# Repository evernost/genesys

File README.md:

# genesys
Audio processing on a custom STM32 board.

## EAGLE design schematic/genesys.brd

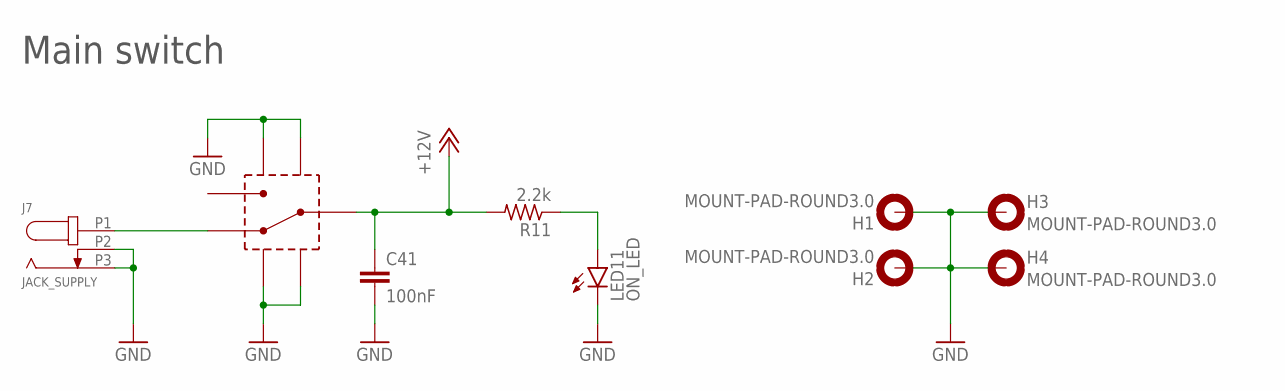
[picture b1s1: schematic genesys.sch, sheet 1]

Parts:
C41: 100nF; C0805K
H1, H2, H3, H4: MOUNT-PAD-ROUND3.0; 3,0-PAD
J7: JACK_SUPPLY; DC-10LP
LED11: ON_LED; CHIPLED_0603
R11: 2.2k; R0603
S1: SWITCH_1P

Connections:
+12V: C41.1, R11.2, S1.P2; also elsewhere on the board
GND: C41.2, H1.B3,0, H2.B3,0, H3.B3,0, H4.B3,0, J7.P2, J7.P3, LED11.C, S1.SHIELD@1 (SHIELD), S1.SHIELD@2 (SHIELD), S1.SHIELD@3 (SHIELD), S1.SHIELD@4 (SHIELD); also elsewhere on the board
unnamed: J7.P1, S1.P1
unnamed: LED11.A, R11.1

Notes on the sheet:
Main switch

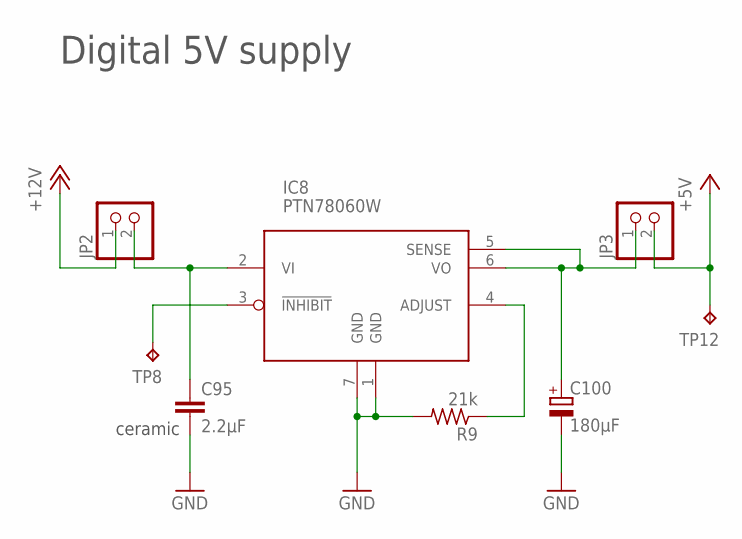
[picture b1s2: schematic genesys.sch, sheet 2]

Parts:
C95: 2.2µF; C1206
C100: 180µF; E3,5-8
IC8: PTN78060W; R-PDSS-T7
JP2, JP3: PINHD-1X2; 1X02
R9: 21k; R0805
TP8, TP12: TPTP15R; TP15R

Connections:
+5V: JP3.2, TP12.TP; also elsewhere on the board
+12V: JP2.1; also elsewhere on the board
GND: C95.2, C100.-, IC8.1 (GND), IC8.7 (GND), R9.2; also elsewhere on the board
unnamed: C95.1, IC8.2 (VI), JP2.2
unnamed: C100.+, IC8.5 (SENSE), IC8.6 (VO), JP3.1
unnamed: IC8.3 (!INHIBIT), TP8.TP
unnamed: IC8.4 (ADJUST), R9.1

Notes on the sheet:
Digital 5V supply
ceramic

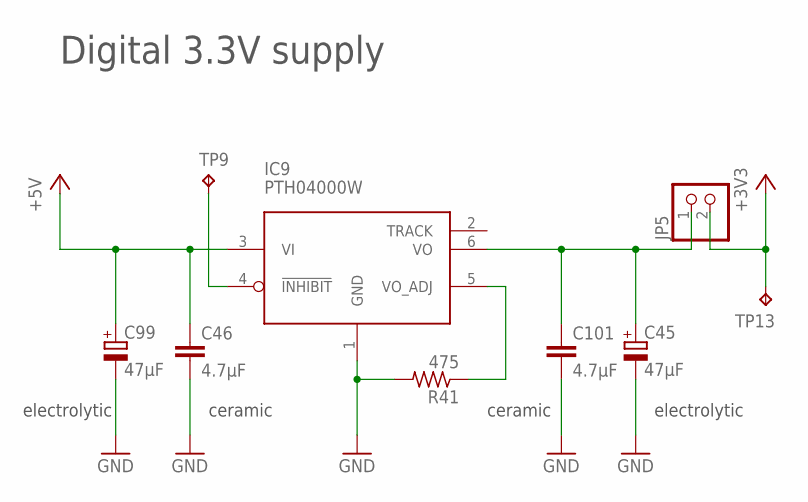
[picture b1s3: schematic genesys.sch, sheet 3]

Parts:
C45, C99: 47µF; E2,5-7
C46, C101: 4.7µF; C0805K
IC9: PTH04000W; R-PDSS-T6
JP5: PINHD-1X2; 1X02
R41: 475; R0805
TP9, TP13: TPTP15R; TP15R

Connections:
+3V3: JP5.2, TP13.TP; also elsewhere on the board
+5V: C46.1, C99.+, IC9.3 (VI); also elsewhere on the board
GND: C45.-, C46.2, C99.-, C101.2, IC9.1 (GND), R41.2; also elsewhere on the board
unnamed: IC9.5 (VO_ADJ), R41.1
unnamed: IC9.4 (!INHIBIT), TP9.TP
unnamed: C45.+, C101.1, IC9.6 (VO), JP5.1
TRACK: IC9.2 (TRACK)

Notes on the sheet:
Digital 3.3V supply
electrolytic
ceramic

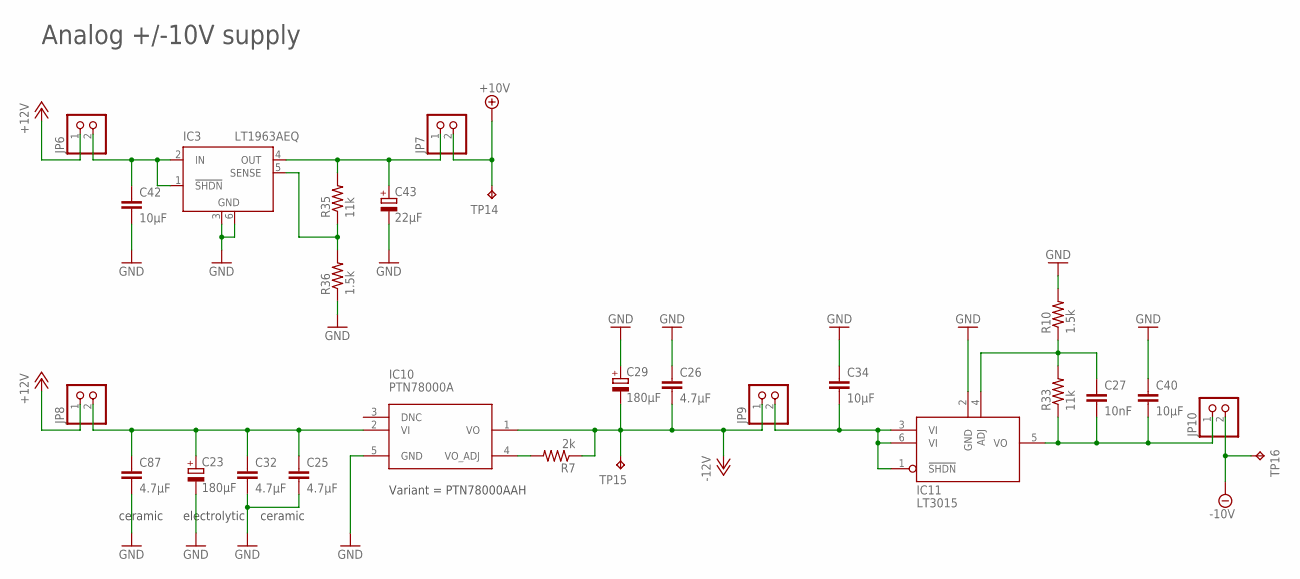
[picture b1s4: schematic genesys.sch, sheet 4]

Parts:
C23, C29: 180µF; E3,5-8
C25, C26, C32, C87: 4.7µF; C0805K
C27: 10nF; C0805K
C34, C40, C42: 10µF; C0805K
C43: 22µF; CT3528
IC3: LT1963AEQ; Q5-DD
IC10: PTN78000A; R-PDSS-T5
IC11: LT3015; Q5-DD
JP6, JP7, JP8, JP9, JP10: PINHD-1X2; 1X02
R7: 2k; R0805
R10, R36: 1.5k; R0805
R33, R35: 11k; R0805
TP14, TP15, TP16: TPTP15R; TP15R

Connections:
+10V: JP7.2, TP14.TP; also elsewhere on the board
+12V: JP6.1, JP8.1; also elsewhere on the board
-10V: JP10.2, TP16.TP; also elsewhere on the board
-12V: C26.2, C29.-, IC10.1 (VO), JP9.1, R7.1, TP15.TP
GND: C23.-, C25.2, C26.1, C29.+, C32.2, C34.1, C40.1, C42.2, C43.-, C87.2, IC3.3 (GND), IC3.6 (GND), IC10.5 (GND), IC11.2 (GND), R10.2, R36.1; also elsewhere on the board
unnamed: IC3.5 (SENSE), R35.1, R36.2
unnamed: IC10.4 (VO_ADJ), R7.2
unnamed: C27.1, IC11.4 (ADJ), R10.1, R33.2
unnamed: C42.1, IC3.1 (!SHDN), IC3.2 (IN), JP6.2
unnamed: C43.+, IC3.4 (OUT), JP7.1, R35.2
unnamed: C34.2, IC11.1 (!SHDN), IC11.3 (VI), IC11.6 (VI), JP9.2
unnamed: C23.+, C25.1, C32.1, C87.1, IC10.2 (VI), JP8.2
unnamed: C27.2, C40.2, IC11.5 (VO), JP10.1, R33.1

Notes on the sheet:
Analog +/-10V supply
ceramic
electrolytic
Variant = PTN78000AAH

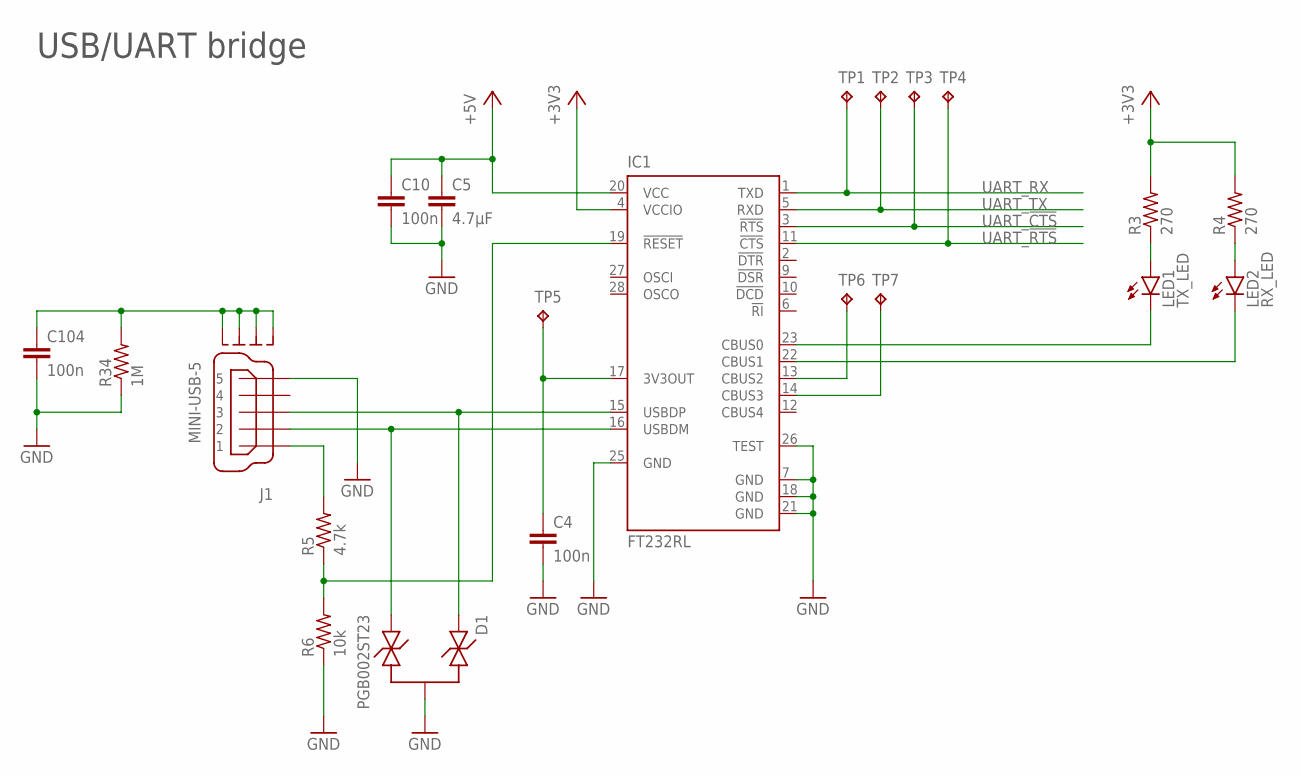
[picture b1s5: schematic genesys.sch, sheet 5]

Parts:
C4, C10, C104: 100n; C0805K
C5: 4.7µF; C0805K
D1: PGB002ST23; SOT23
IC1: FT232RL; SSOP28
J1: MINI-USB-5; 56579-0579
LED1: TX_LED; CHIPLED_0603
LED2: RX_LED; CHIPLED_0603
R3, R4: 270; R0603
R5: 4.7k; R0603
R6: 10k; R0603
R34: 1M; R0603
TP1, TP2, TP3, TP4, TP5, TP6, TP7: TPTP15R; TP15R

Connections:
+3V3: IC1.4 (VCCIO), R3.2, R4.2; also elsewhere on the board
+5V: C5.1, C10.1, IC1.20 (VCC); also elsewhere on the board
GND: C4.2, C5.2, C10.2, C104.2, D1.3, IC1.7 (GND), IC1.18 (GND), IC1.21 (GND), IC1.25 (GND), IC1.26 (TEST), J1.GND (5), R6.1, R34.1; also elsewhere on the board
unnamed: C4.1, IC1.17 (3V3OUT), TP5.TP
unnamed: IC1.23 (CBUS0), LED1.C
unnamed: IC1.22 (CBUS1), LED2.C
unnamed: LED1.A, R3.1
unnamed: LED2.A, R4.1
unnamed: D1.2, IC1.16 (USBDM), J1.DN (2)
unnamed: J1.VBUS (1), R5.2
unnamed: IC1.19 (!RESET), R5.1, R6.2
unnamed: D1.1, IC1.15 (USBDP), J1.DP (3)
unnamed: IC1.13 (CBUS2), TP6.TP
unnamed: IC1.14 (CBUS3), TP7.TP
unnamed: C104.1, J1.SHIELD@1 (S1), J1.SHIELD@2 (S2), J1.SHIELD@3 (S3), J1.SHIELD@4 (S4), R34.2
UART_!CTS: IC1.3 (!RTS), TP3.TP; also elsewhere on the board
UART_!RTS: IC1.11 (!CTS), TP4.TP; also elsewhere on the board
UART_RX: IC1.1 (TXD), TP1.TP; also elsewhere on the board
UART_TX: IC1.5 (RXD), TP2.TP; also elsewhere on the board

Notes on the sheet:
USB/UART bridge

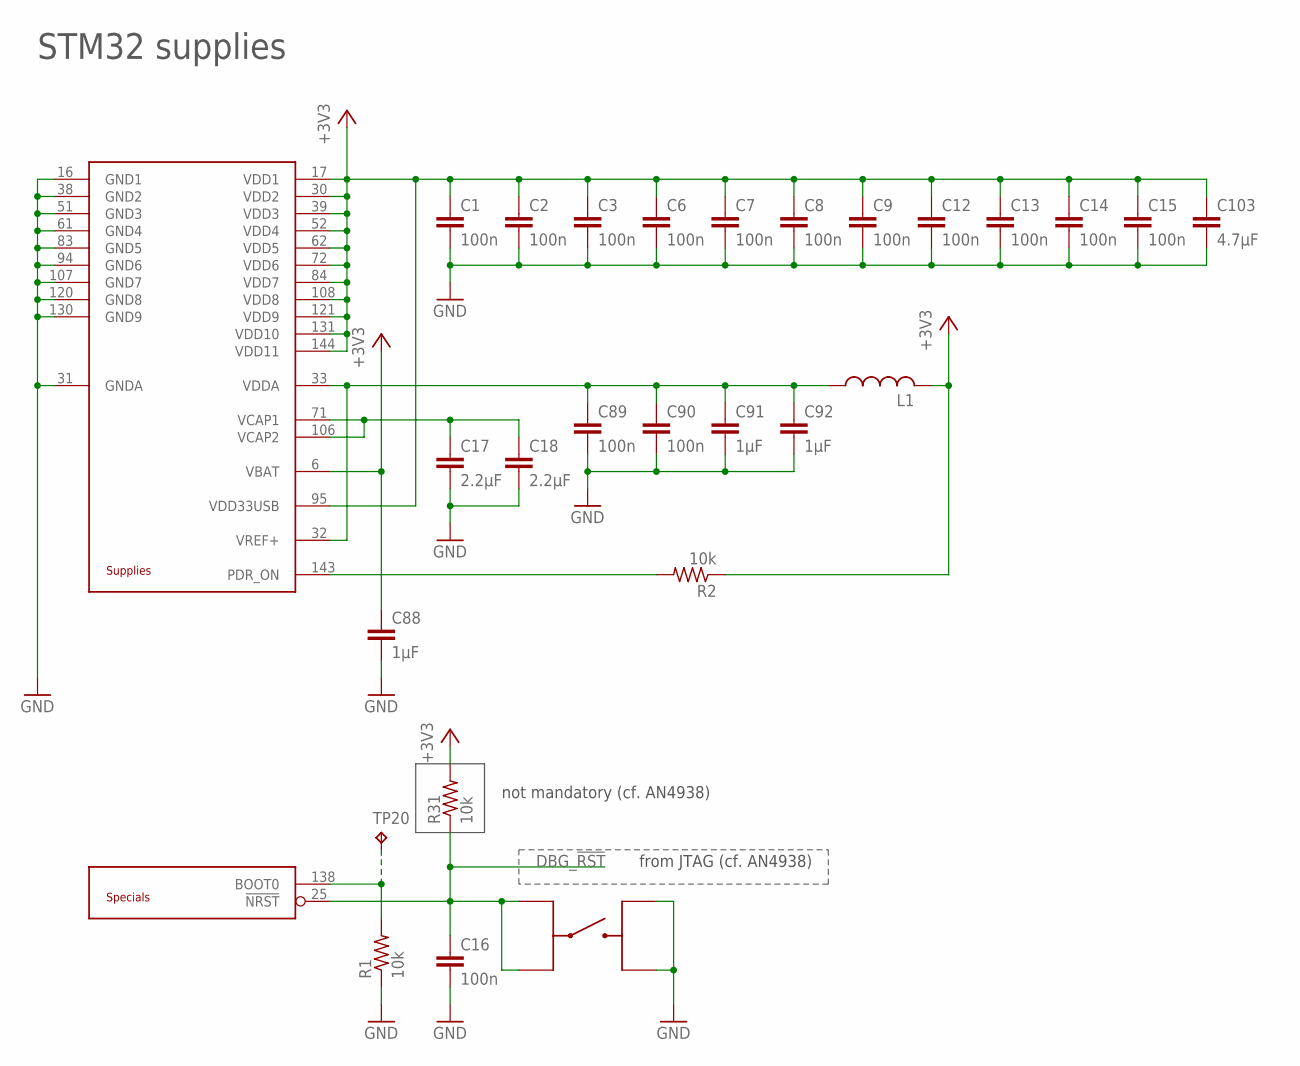
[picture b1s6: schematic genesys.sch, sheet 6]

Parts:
B1: KSC521G
C1, C2, C3, C6, C7, C8, C9, C12, C13, C14, C15, C16, C89, C90: 100n; C0805K
C17, C18: 2.2µF; C0805K
C88, C91, C92: 1µF; C0805K
C103: 4.7µF; C0805K
L1: L-USL3216C; L3216C
R1, R2, R31: 10k; R0805
TP20: TPTP15R; TP15R
U$1: STM32H743ZI; TQFP144

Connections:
+3V3: C1.1, C2.1, C3.1, C6.1, C7.1, C8.1, C9.1, C12.1, C13.1, C14.1, C15.1, C88.1, C103.1, L1.2, R2.1, R31.2, U$1.6 (VBAT), U$1.17 (VDD1), U$1.30 (VDD2), U$1.39 (VDD3), U$1.52 (VDD4), U$1.62 (VDD5), U$1.72 (VDD6), U$1.84 (VDD7), U$1.95 (VDD33USB), U$1.108 (VDD8), U$1.121 (VDD9), U$1.131 (VDD10), U$1.144 (VDD11); also elsewhere on the board
DBG_!RST: B1.3, B1.4, C16.1, R31.1, U$1.25 (!NRST); also elsewhere on the board
GND: B1.1, B1.2, C1.2, C2.2, C3.2, C6.2, C7.2, C8.2, C9.2, C12.2, C13.2, C14.2, C15.2, C16.2, C17.2, C18.2, C88.2, C89.2, C90.2, C91.2, C92.2, C103.2, R1.1, U$1.16 (GND1), U$1.31 (GNDA), U$1.38 (GND2), U$1.51 (GND3), U$1.61 (GND4), U$1.83 (GND5), U$1.94 (GND6), U$1.107 (GND7), U$1.120 (GND8), U$1.130 (GND9); also elsewhere on the board
unnamed: R1.2, TP20.TP, U$1.138 (BOOT0)
unnamed: C89.1, C90.1, C91.1, C92.1, L1.1, U$1.32 (VREF+), U$1.33 (VDDA)
unnamed: R2.2, U$1.143 (PDR_ON)
unnamed: C17.1, C18.1, U$1.71 (VCAP1), U$1.106 (VCAP2)

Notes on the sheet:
STM32 supplies
not mandatory (cf. AN4938)
from JTAG (cf. AN4938)

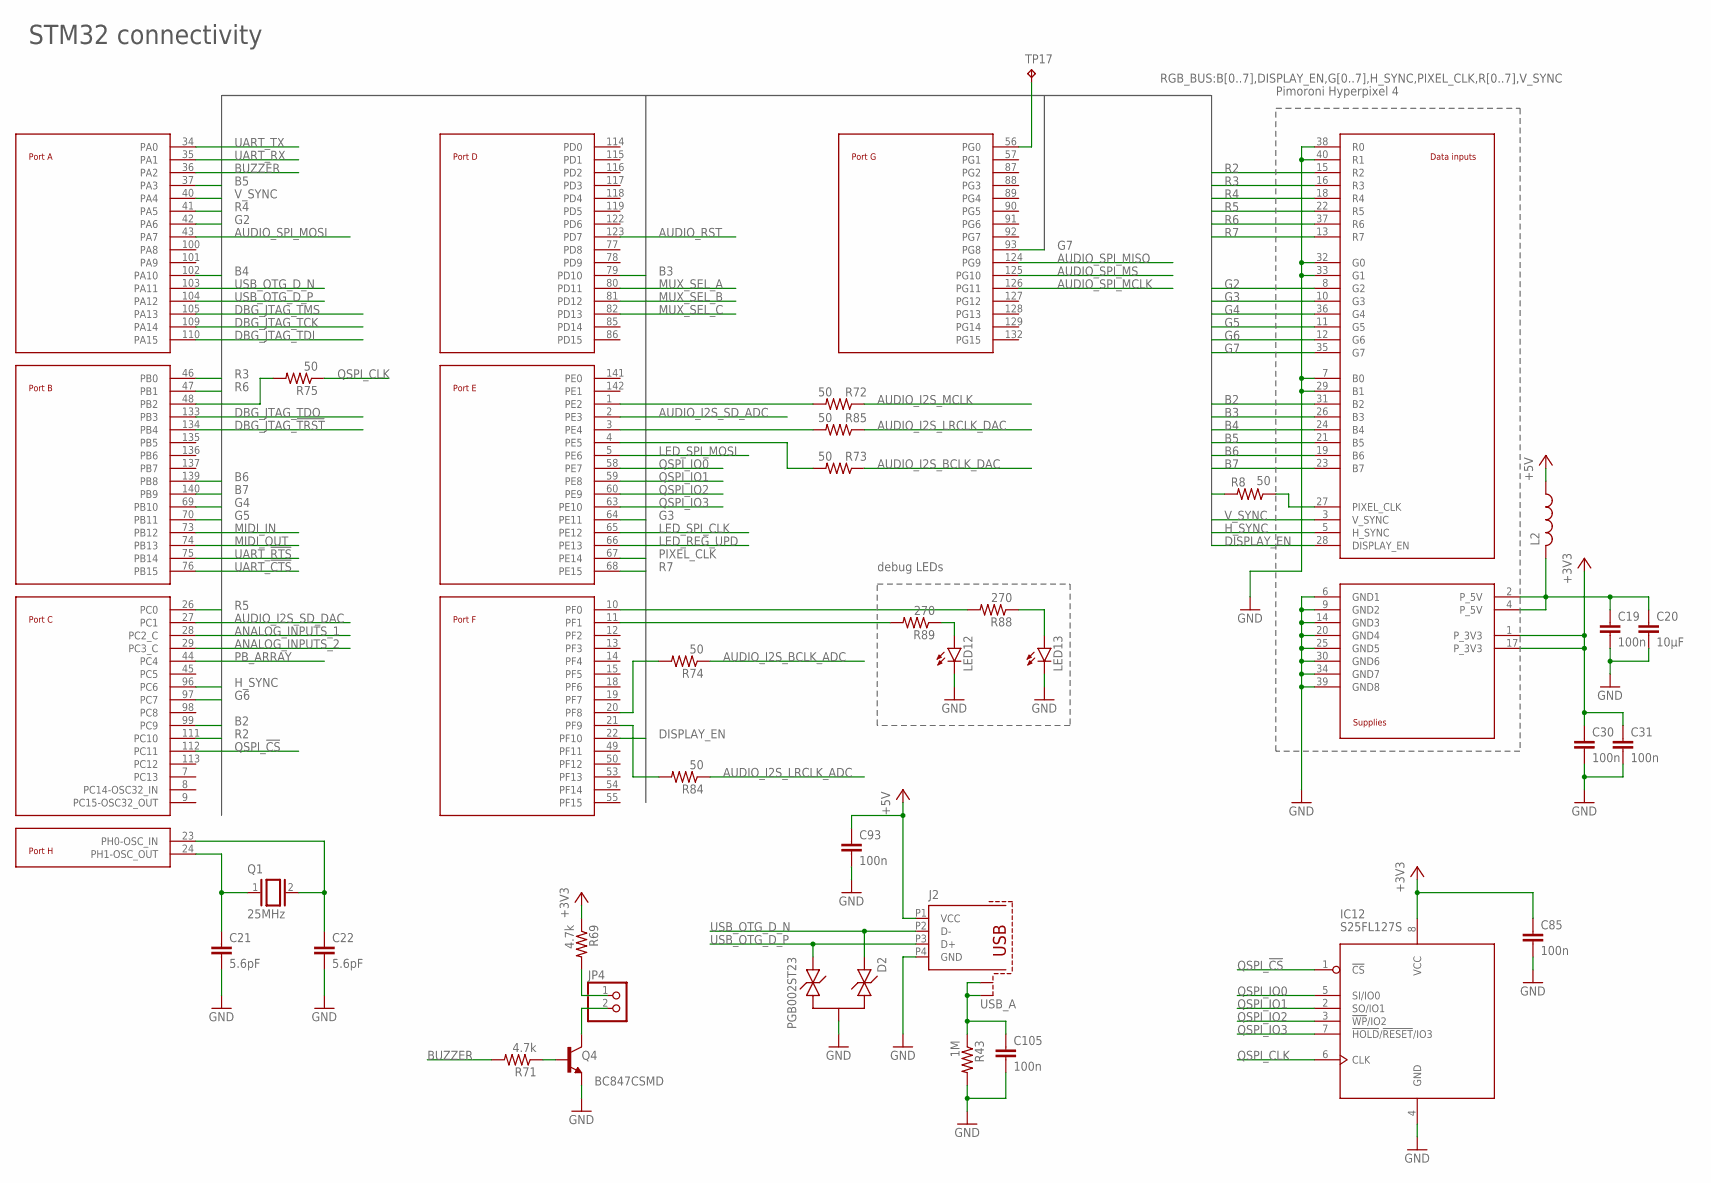
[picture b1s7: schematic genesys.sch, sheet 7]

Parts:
C19, C30, C31, C85, C93, C105: 100n; C0805K
C20: 10µF; C0805K
C21, C22: 5.6pF; C0805K
D2: PGB002ST23; SOT23
IC12: S25FL127S; SO8
J2: USB_A
JP4: PINHD-1X2; 1X02
L2: L-USL3216C; L3216C
LED12, LED13: USR_LED_1; CHIPLED_0603
Q1: 25MHz; QS
Q4: BC847CSMD; SOT23
R8: 50; R0805
R43: 1M; R0603
R69, R71: 4.7k; R0805
R72, R73, R74, R75, R84, R85: 50; R0603
R88, R89: 270; R0603
TP17: TPTP15R; TP15R
U$1: STM32H743ZI; TQFP144
U$2: HYPERPIXEL4.0

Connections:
+3V3: C30.1, C31.1, C85.1, IC12.8 (VCC), R69.1, U$2.1 (P_3V3), U$2.17 (P_3V3); also elsewhere on the board
+5V: C93.1, J2.P1 (VCC), L2.1; also elsewhere on the board
ANALOG_INPUTS_1: U$1.28 (PC2_C); also elsewhere on the board
ANALOG_INPUTS_2: U$1.29 (PC3_C); also elsewhere on the board
AUDIO_I2S_BCLK_ADC: R74.1; also elsewhere on the board
AUDIO_I2S_BCLK_DAC: R73.1; also elsewhere on the board
AUDIO_I2S_LRCLK_ADC: R84.1; also elsewhere on the board
AUDIO_I2S_LRCLK_DAC: R85.1; also elsewhere on the board
AUDIO_I2S_MCLK: R72.1; also elsewhere on the board
AUDIO_I2S_SD_ADC: U$1.2 (PE3); also elsewhere on the board
AUDIO_I2S_SD_DAC: U$1.27 (PC1); also elsewhere on the board
AUDIO_RST: U$1.123 (PD7); also elsewhere on the board
AUDIO_SPI_MCLK: U$1.126 (PG11); also elsewhere on the board
AUDIO_SPI_MISO: U$1.124 (PG9); also elsewhere on the board
AUDIO_SPI_MOSI: U$1.43 (PA7); also elsewhere on the board
AUDIO_SPI_MS: U$1.125 (PG10); also elsewhere on the board
B2: U$1.99 (PC9), U$2.31 (B2)
B3: U$1.79 (PD10), U$2.26 (B3)
B4: U$1.102 (PA10), U$2.24 (B4)
B5: U$1.37 (PA3), U$2.21 (B5)
B6: U$1.139 (PB8), U$2.19 (B6)
B7: U$1.140 (PB9), U$2.23 (B7)
BUZZER: R71.2, U$1.36 (PA2)
DBG_JTAG_!TRST: U$1.134 (PB4); also elsewhere on the board
DBG_JTAG_TCK: U$1.109 (PA14); also elsewhere on the board
DBG_JTAG_TDI: U$1.110 (PA15); also elsewhere on the board
DBG_JTAG_TDO: U$1.133 (PB3); also elsewhere on the board
DBG_JTAG_TMS: U$1.105 (PA13); also elsewhere on the board
DISPLAY_EN: U$1.22 (PF10), U$2.28 (DISPLAY_EN)
G2: U$1.42 (PA6), U$2.8 (G2)
G3: U$1.64 (PE11), U$2.10 (G3)
G4: U$1.69 (PB10), U$2.36 (G4)
G5: U$1.70 (PB11), U$2.11 (G5)
G6: U$1.97 (PC7), U$2.12 (G6)
G7: U$1.93 (PG8), U$2.35 (G7)
GND: C19.2, C20.2, C21.2, C22.2, C30.2, C31.2, C85.2, C93.2, C105.2, D2.3, IC12.4 (GND), J2.P4 (GND), LED12.C, LED13.C, Q4.2 (E), R43.2, U$2.6 (GND1), U$2.7 (B0), U$2.9 (GND2), U$2.14 (GND3), U$2.20 (GND4), U$2.25 (GND5), U$2.29 (B1), U$2.30 (GND6), U$2.32 (G0), U$2.33 (G1), U$2.34 (GND7), U$2.38 (R0), U$2.39 (GND8), U$2.40 (R1); also elsewhere on the board
H_SYNC: U$1.96 (PC6), U$2.5 (H_SYNC)
LED_REG_UPD: U$1.66 (PE13); also elsewhere on the board
LED_SPI_CLK: U$1.65 (PE12); also elsewhere on the board
LED_SPI_MOSI: U$1.5 (PE6); also elsewhere on the board
MIDI_IN: U$1.73 (PB12); also elsewhere on the board
MIDI_OUT: U$1.74 (PB13); also elsewhere on the board
MUX_SEL_A: U$1.80 (PD11); also elsewhere on the board
MUX_SEL_B: U$1.81 (PD12); also elsewhere on the board
MUX_SEL_C: U$1.82 (PD13); also elsewhere on the board
unnamed: R8.1, U$2.27 (PIXEL_CLK)
unnamed: C21.1, Q1.1, U$1.24 (PH1-OSC_OUT)
unnamed: C22.1, Q1.2, U$1.23 (PH0-OSC_IN)
unnamed: C19.1, C20.1, L2.2, U$2.2 (P_5V), U$2.4 (P_5V)
unnamed: R88.2, U$1.10 (PF0)
unnamed: R89.2, U$1.11 (PF1)
unnamed: LED12.A, R89.1
unnamed: LED13.A, R88.1
unnamed: C105.1, J2.SHIELD@1 (S1), J2.SHIELD@2 (S2), R43.1
unnamed: JP4.1, R69.2
unnamed: JP4.2, Q4.3 (C)
unnamed: R72.2, U$1.1 (PE2)
unnamed: Q4.1 (B), R71.1
unnamed: R73.2, U$1.4 (PE5)
unnamed: R74.2, U$1.20 (PF8)
unnamed: R75.2, U$1.48 (PB2)
unnamed: TP17.TP, U$1.56 (PG0)
unnamed: R84.2, U$1.21 (PF9)
unnamed: R85.2, U$1.3 (PE4)
PB_ARRAY: U$1.44 (PC4); also elsewhere on the board
PIXEL_CLK: R8.2, U$1.67 (PE14)
QSPI_!CS: IC12.1 (!CS), U$1.112 (PC11)
QSPI_CLK: IC12.6 (CLK), R75.1
QSPI_IO0: IC12.5 (SI/IO0), U$1.58 (PE7)
QSPI_IO1: IC12.2 (SO/IO1), U$1.59 (PE8)
QSPI_IO2: IC12.3 (!WP!/IO2), U$1.60 (PE9)
QSPI_IO3: IC12.7 (!HOLD!/!RESET!/IO3), U$1.63 (PE10)
R2: U$1.111 (PC10), U$2.15 (R2)
R3: U$1.46 (PB0), U$2.16 (R3)
R4: U$1.41 (PA5), U$2.18 (R4)
R5: U$1.26 (PC0), U$2.22 (R5)
R6: U$1.47 (PB1), U$2.37 (R6)
R7: U$1.68 (PE15), U$2.13 (R7)
UART_!CTS: U$1.76 (PB15); also elsewhere on the board
UART_!RTS: U$1.75 (PB14); also elsewhere on the board
UART_RX: U$1.35 (PA1); also elsewhere on the board
UART_TX: U$1.34 (PA0); also elsewhere on the board
USB_OTG_D_N: D2.1, J2.P2 (D-), U$1.103 (PA11)
USB_OTG_D_P: D2.2, J2.P3 (D+), U$1.104 (PA12)
V_SYNC: U$1.40 (PA4), U$2.3 (V_SYNC)

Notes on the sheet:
STM32 connectivity
Pimoroni Hyperpixel 4
debug LEDs

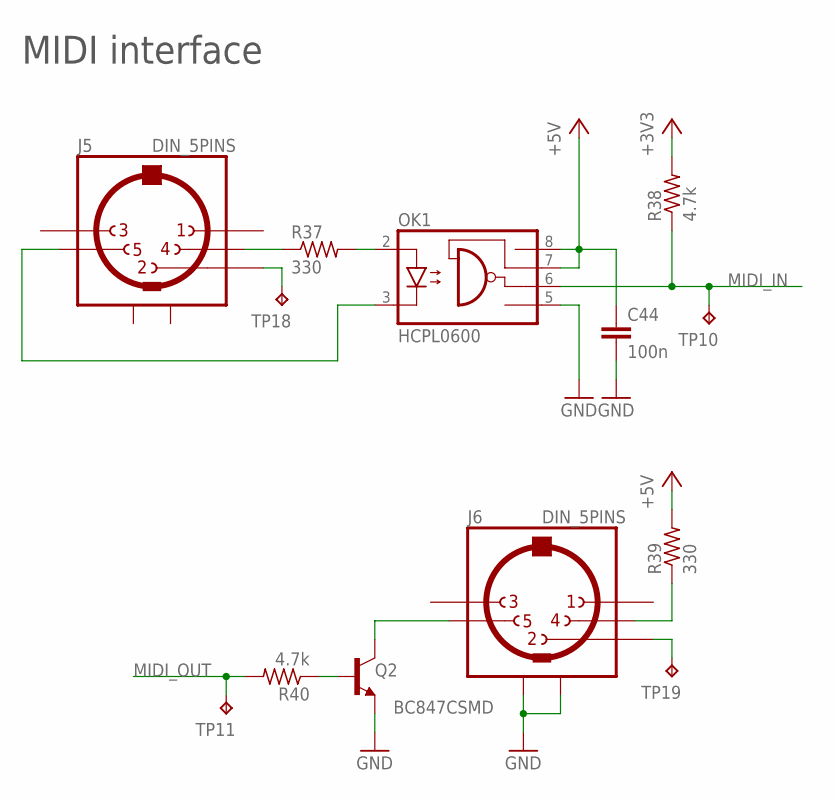
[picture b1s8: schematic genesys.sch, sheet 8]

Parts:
C44: 100n; C0805K
J5, J6: DIN_5PINS; 71251-050/0800
OK1: HCPL0600; SOIC08
Q2: BC847CSMD; SOT23
R37, R39: 330; R0805
R38, R40: 4.7k; R0805
TP10, TP11, TP18, TP19: TPTP15R; TP15R

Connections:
+3V3: R38.2; also elsewhere on the board
+5V: C44.1, OK1.7 (VE), OK1.8 (VCC), R39.2; also elsewhere on the board
GND: C44.2, J6.GND@1 (SHIELD), J6.GND@2 (SHIELD), OK1.5 (GND), Q2.2 (E); also elsewhere on the board
MIDI_IN: OK1.6 (VO), R38.1, TP10.TP; also elsewhere on the board
MIDI_OUT: R40.2, TP11.TP; also elsewhere on the board
unnamed: J6.P4 (4), R39.1
unnamed: OK1.2 (A), R37.2
unnamed: J5.P5 (5), OK1.3 (C)
unnamed: J5.P4 (4), R37.1
unnamed: J6.P5 (5), Q2.3 (C)
unnamed: Q2.1 (B), R40.1
unnamed: J5.P2 (2), TP18.TP
unnamed: J6.P2 (2), TP19.TP
SHIELD: J5.GND@1 (SHIELD), J5.GND@2 (SHIELD)

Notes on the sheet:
MIDI interface

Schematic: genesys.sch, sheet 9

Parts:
C28, C33: 100n; C0805K
IC2, IC13: 4051D; SO16
JP11: PINHD-1X6; 1X06
P1, P2, P3, P4, P5, P6: PTV09F2M; EVUFXM
P7: JOYSTICK_XY; RKJXK1210002

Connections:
+3V3: C28.1, C33.1, IC2.16 (VCC), IC13.16 (VCC), JP11.1, P1.3 (E), P2.3 (E), P3.3 (E), P4.3 (E), P5.3 (E), P6.3 (E), P7.PX3, P7.PY3; also elsewhere on the board
ANALOG_INPUTS_1: IC2.3 (X); also elsewhere on the board
ANALOG_INPUTS_2: IC13.3 (X); also elsewhere on the board
GND: C28.2, C33.2, IC2.2 (X6), IC2.4 (X7), IC2.6 (INH), IC2.7 (VEE), IC2.8 (GND), IC13.2 (X6), IC13.4 (X7), IC13.6 (INH), IC13.7 (VEE), IC13.8 (GND), JP11.6, P1.1 (A), P2.1 (A), P3.1 (A), P4.1 (A), P5.1 (A), P6.1 (A), P7.PX1, P7.PY1, P7.SHIELD@1 (SHIELD), P7.SHIELD@2 (SHIELD), P7.SHIELD@3 (SHIELD), P7.SHIELD@4 (SHIELD); also elsewhere on the board
MUX_SEL_A: IC2.11 (A), IC13.11 (A); also elsewhere on the board
MUX_SEL_B: IC2.10 (B), IC13.10 (B); also elsewhere on the board
MUX_SEL_C: IC2.9 (C), IC13.9 (C); also elsewhere on the board
unnamed: IC2.12 (X3), P4.2 (S)
unnamed: IC2.15 (X2), P3.2 (S)
unnamed: IC2.14 (X1), P2.2 (S)
unnamed: IC2.13 (X0), P1.2 (S)
unnamed: IC2.1 (X4), P5.2 (S)
unnamed: IC13.14 (X1), P7.PX2
unnamed: IC2.5 (X5), P6.2 (S)
unnamed: IC13.15 (X2), JP11.5
unnamed: IC13.12 (X3), JP11.4
unnamed: IC13.13 (X0), P7.PY2
unnamed: IC13.1 (X4), JP11.3
unnamed: IC13.5 (X5), JP11.2

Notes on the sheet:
User inputs (analog)
reference = PTV09A-4015U-B103

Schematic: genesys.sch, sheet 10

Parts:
C86: 100n; C0805K
IC7: 74HC595D; SO16
LED3: USR_LED_1; CHIPLED_0603
LED4: USR_LED_2; CHIPLED_0603
LED5: USR_LED_3; CHIPLED_0603
LED6: USR_LED_4; CHIPLED_0603
LED7: USR_LED_5; CHIPLED_0603
LED8: USR_LED_6; CHIPLED_0603
LED9: USR_LED_7; CHIPLED_0603
LED10: USR_LED_8; CHIPLED_0603
R76, R77, R78, R79, R80, R81, R82, R83: 270; R0603

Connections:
+3V3: C86.1, IC7.10 (SCL), IC7.16 (VCC); also elsewhere on the board
GND: C86.2, IC7.8 (GND), IC7.13 (G), LED3.C, LED4.C, LED5.C, LED6.C, LED7.C, LED8.C, LED9.C, LED10.C; also elsewhere on the board
LED_REG_UPD: IC7.12 (RCK); also elsewhere on the board
LED_SPI_CLK: IC7.11 (SCK); also elsewhere on the board
LED_SPI_MOSI: IC7.14 (SER); also elsewhere on the board
unnamed: LED3.A, R76.1
unnamed: LED4.A, R77.1
unnamed: IC7.1 (QB), R77.2
unnamed: IC7.15 (QA), R76.2
unnamed: LED5.A, R78.1
unnamed: LED6.A, R79.1
unnamed: IC7.3 (QD), R79.2
unnamed: IC7.2 (QC), R78.2
unnamed: LED7.A, R80.1
unnamed: LED8.A, R81.1
unnamed: IC7.5 (QF), R81.2
unnamed: IC7.4 (QE), R80.2
unnamed: LED9.A, R82.1
unnamed: LED10.A, R83.1
unnamed: IC7.7 (QH), R83.2
unnamed: IC7.6 (QG), R82.2

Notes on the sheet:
UI LEDs

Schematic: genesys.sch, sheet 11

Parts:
B2, B3, B4, B5, B6, B7, B8: KSC521G
C24, C35, C36, C37, C38, C39, C94: 100nF; C0805K
C102: 100n; C0805K
IC15: 4067D; SO24W
R12, R13, R20, R22, R24, R26, R28: 10k; R0805
R14, R21, R23, R25, R27, R29, R32: 330; R0805

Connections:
+3V3: B2.1, B2.2, B3.1, B3.2, B4.1, B4.2, B5.1, B5.2, B6.1, B6.2, B7.1, B7.2, B8.1, B8.2, C102.1, IC15.24 (VDD); also elsewhere on the board
GND: C24.2, C35.2, C36.2, C37.2, C38.2, C39.2, C94.2, C102.2, IC15.2 (X7), IC15.12 (VSS), IC15.13 (D), IC15.15 (INH), IC15.16 (X15), IC15.17 (X14), IC15.18 (X13), IC15.19 (X12), IC15.20 (X11), IC15.21 (X10), IC15.22 (X9), IC15.23 (X8), R12.2, R13.2, R20.2, R22.2, R24.2, R26.2, R28.2; also elsewhere on the board
MUX_SEL_A: IC15.10 (A); also elsewhere on the board
MUX_SEL_B: IC15.11 (B); also elsewhere on the board
MUX_SEL_C: IC15.14 (C); also elsewhere on the board
unnamed: C35.1, IC15.6 (X3), R21.1
unnamed: B3.3, B3.4, R20.1, R21.2
unnamed: B5.3, B5.4, R22.1, R23.2
unnamed: B6.3, B6.4, R24.1, R25.2
unnamed: B7.3, B7.4, R26.1, R27.2
unnamed: B8.3, B8.4, R28.1, R29.2
unnamed: B4.3, B4.4, R12.1, R32.2
unnamed: B2.3, B2.4, R13.1, R14.2
PB_2: C36.1, IC15.7 (X2), R23.1
PB_3: C37.1, IC15.4 (X5), R25.1
PB_4: C38.1, IC15.3 (X6), R27.1
PB_5: C39.1, IC15.5 (X4), R29.1
PB_6: C24.1, IC15.8 (X1), R14.1
PB_7: C94.1, IC15.9 (X0), R32.1
PB_ARRAY: IC15.1 (X); also elsewhere on the board

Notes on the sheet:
User inputs (digital)

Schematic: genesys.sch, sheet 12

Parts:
C106: 100n; C0805K
JP1: PINHD-2X10; 2X10
R15, R16, R17, R18, R19, R30: 22; R0805
R86, R87, R90: 10k; R0805

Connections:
+3V3: C106.1, JP1.1, JP1.2; also elsewhere on the board
DBG_!RST: R30.1; also elsewhere on the board
DBG_JTAG_!TRST: R15.1; also elsewhere on the board
DBG_JTAG_TCK: R18.1; also elsewhere on the board
DBG_JTAG_TDI: R16.1; also elsewhere on the board
DBG_JTAG_TDO: R19.1; also elsewhere on the board
DBG_JTAG_TMS: R17.1; also elsewhere on the board
GND: C106.2, JP1.4, JP1.6, JP1.8, JP1.10, JP1.12, JP1.14, JP1.16, JP1.18, JP1.20, R86.1, R87.1, R90.1; also elsewhere on the board
unnamed: JP1.3, R15.2
unnamed: JP1.5, R16.2
unnamed: JP1.7, R17.2
unnamed: JP1.9, R18.2
unnamed: JP1.13, R19.2
unnamed: JP1.15, R30.2
unnamed: JP1.19, R90.2
unnamed: JP1.17, R87.2
unnamed: JP1.11, R86.2

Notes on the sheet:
Debug interface (SWD)

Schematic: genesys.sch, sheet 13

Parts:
C11, C49, C51, C52, C53, C54, C59, C96, C97, C98: 10µF; C0805K
C48, C50, C55, C56, C57, C58: 1µF; C0805K
U$8: PCM3168A; HTQFP64

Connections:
+3V3: C11.1, C48.1, C49.1, C50.1, U$8.12 (VDD), U$8.46 (VDD); also elsewhere on the board
+5V: C55.1, C56.1, C57.1, C58.1, C59.1, C96.1, C97.1, C98.1, U$8.3 (VCCAD), U$8.14 (VCCDA), U$8.34 (VCCDA), U$8.49 (VCCAD); also elsewhere on the board
GND: C11.2, C48.2, C49.2, C50.2, C51.2, C52.2, C53.2, C54.2, C55.2, C56.2, C57.2, C58.2, C59.2, C96.2, C97.2, C98.2, U$8.2 (AGNDAD), U$8.11 (DGND), U$8.16 (AGNDDA), U$8.33 (AGNDDA), U$8.47 (DGND), U$8.50 (AGNDAD), U$8.GND (GND_PAD); also elsewhere on the board
unnamed: C51.1, U$8.60 (VREFAD)
unnamed: C52.1, U$8.59 (VREFAD)
unnamed: C53.1, U$8.15 (VCOMDA)
VCOMAD: C54.1, U$8.1 (VCOMAD); also elsewhere on the board

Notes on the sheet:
ADC/DAC (supplies)

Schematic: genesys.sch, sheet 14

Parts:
R70: 0; R0805
U$8: PCM3168A; HTQFP64

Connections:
+3V3: R70.1; also elsewhere on the board
AUDIO_I2S_BCLK_ADC: U$8.7 (BCKAD); also elsewhere on the board
AUDIO_I2S_BCLK_DAC: U$8.36 (BCKDA); also elsewhere on the board
AUDIO_I2S_LRCLK_ADC: U$8.6 (LRCKAD); also elsewhere on the board
AUDIO_I2S_LRCLK_DAC: U$8.35 (LRCKDA); also elsewhere on the board
AUDIO_I2S_MCLK: U$8.41 (SCKI); also elsewhere on the board
AUDIO_I2S_SD_ADC: U$8.8 (DOUT1); also elsewhere on the board
AUDIO_I2S_SD_DAC: U$8.37 (DIN1); also elsewhere on the board
AUDIO_RST: U$8.4 (RST); also elsewhere on the board
AUDIO_SPI_MCLK: U$8.42 (MC/SCL/FMT); also elsewhere on the board
AUDIO_SPI_MISO: U$8.44 (MDO/ADR1/MD1); also elsewhere on the board
AUDIO_SPI_MOSI: U$8.43 (MDI/SDA/DEMP); also elsewhere on the board
AUDIO_SPI_MS: U$8.45 (MS/ADR0/MD0); also elsewhere on the board
GND: U$8.38 (DIN2), U$8.39 (DIN3), U$8.40 (DIN4); also elsewhere on the board
unnamed: R70.2, U$8.48 (MODE)

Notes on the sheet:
ADC/DAC (digital interface)
PCM3168A

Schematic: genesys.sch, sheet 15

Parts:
C47, C62, C66, C70, C71, C72: 100n; C0805K
C60, C64: 2.2n; C0805K
C61, C65: 22p; C0805K
C63, C67: 10n; C0805K
C68, C69: 10µF; C0805K
IC4, IC5: NE5532D; SO08
J3: JACK_6.35
R42, R45, R46, R48, R50, R51: 1.5k; R0805
R44, R47, R49, R52: 47; R0805
R53, R54: 3k; R0805
U$8: PCM3168A; HTQFP64

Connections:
+10V: C47.1, C71.1, IC4.8 (V+), IC5.8 (V+); also elsewhere on the board
-10V: C70.2, C72.2, IC4.4 (V-), IC5.4 (V-); also elsewhere on the board
GND: C47.2, C62.1, C66.1, C70.1, C71.2, C72.1, J3.P4; also elsewhere on the board
unnamed: C60.1, IC4.6 (-IN), R42.2, R53.1
unnamed: C60.2, IC4.7 (OUT), R44.2
unnamed: C63.1, R42.1, R44.1, R45.2, U$8.51 (VIN1-)
unnamed: C61.1, IC4.2 (-IN), R45.1, R46.2
unnamed: C61.2, IC4.1 (OUT), R47.2
unnamed: C64.1, IC5.6 (-IN), R48.2, R54.1
unnamed: C64.2, IC5.7 (OUT), R49.2
unnamed: C67.1, R48.1, R49.1, R50.2, U$8.53 (VIN2-)
unnamed: C65.1, IC5.2 (-IN), R50.1, R51.2
unnamed: C65.2, IC5.1 (OUT), R52.2
unnamed: C69.2, R54.2
unnamed: C67.2, R51.1, R52.1, U$8.54 (VIN2+)
unnamed: C68.2, R53.2
unnamed: C63.2, R46.1, R47.1, U$8.52 (VIN1+)
unnamed: C68.1, J3.P5
unnamed: C69.1, J3.P6
VCOMAD: C62.2, C66.2, IC4.3 (+IN), IC4.5 (+IN), IC5.3 (+IN), IC5.5 (+IN), U$8.55 (VIN3-), U$8.56 (VIN3+), U$8.57 (VIN4-), U$8.58 (VIN4+), U$8.61 (VIN5-), U$8.62 (VIN5+), U$8.63 (VIN6-), U$8.64 (VIN6+); also elsewhere on the board

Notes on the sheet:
ADC/DAC (analog input interface)

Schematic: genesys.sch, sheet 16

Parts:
C73, C74, C78, C79: 10µF; C0805K
C75, C80: 3.3nF; C0805K
C76, C77, C81, C82: 680pF; C0805K
C83, C84: 100n; C0805K
IC6: NE5532D; SO08
J4: JACK_6.35
R55, R56, R62, R63: 7.5k; R0805
R57, R58, R64, R65: 360; R0805
R59, R60, R66, R67: 5.6k; R0805
R61, R68: 47; R0805
U$8: PCM3168A; HTQFP64

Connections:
+10V: C83.1, IC6.8 (V+); also elsewhere on the board
-10V: C84.2, IC6.4 (V-); also elsewhere on the board
GND: C76.1, C81.1, C83.2, C84.1, J4.P4, R59.2, R66.2; also elsewhere on the board
unnamed: C78.1, U$8.30 (VOUT2-)
unnamed: C75.1, R56.1, R58.2, R59.1
unnamed: C75.2, R55.1, R57.2, R60.2
unnamed: C73.2, R55.2
unnamed: C74.2, R56.2
unnamed: C77.2, IC6.2 (-IN), R57.1
unnamed: C76.2, IC6.3 (+IN), R58.1
unnamed: C77.1, IC6.1 (OUT), R60.1, R61.2
unnamed: J4.P5, R61.1
unnamed: C74.1, U$8.31 (VOUT1+)
unnamed: C73.1, U$8.32 (VOUT1-)
unnamed: C80.1, R63.1, R65.2, R66.1
unnamed: C80.2, R62.1, R64.2, R67.2
unnamed: C78.2, R62.2
unnamed: C79.2, R63.2
unnamed: C82.2, IC6.6 (-IN), R64.1
unnamed: C81.2, IC6.5 (+IN), R65.1
unnamed: C82.1, IC6.7 (OUT), R67.1, R68.2
unnamed: J4.P6, R68.1
unnamed: C79.1, U$8.29 (VOUT2+)

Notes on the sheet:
ADC/DAC (analog output interface)

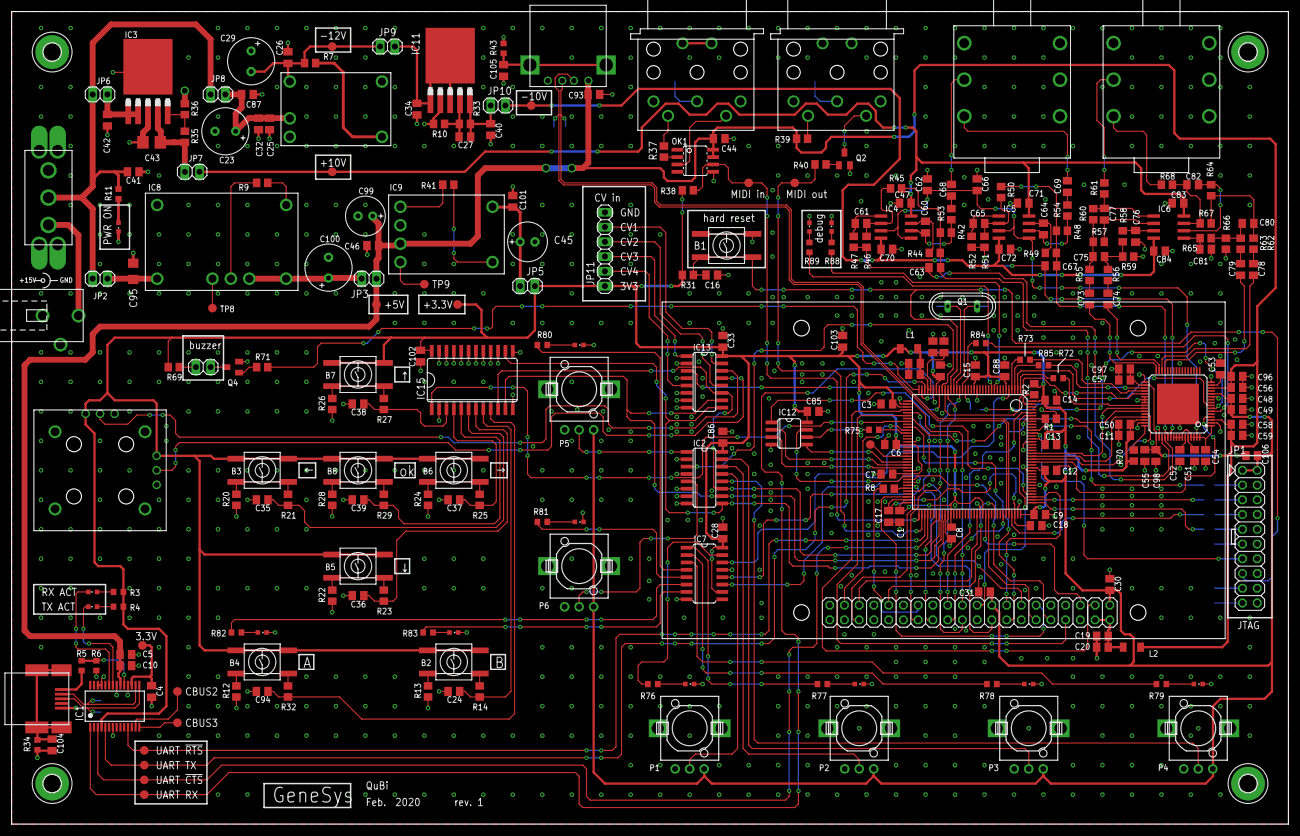
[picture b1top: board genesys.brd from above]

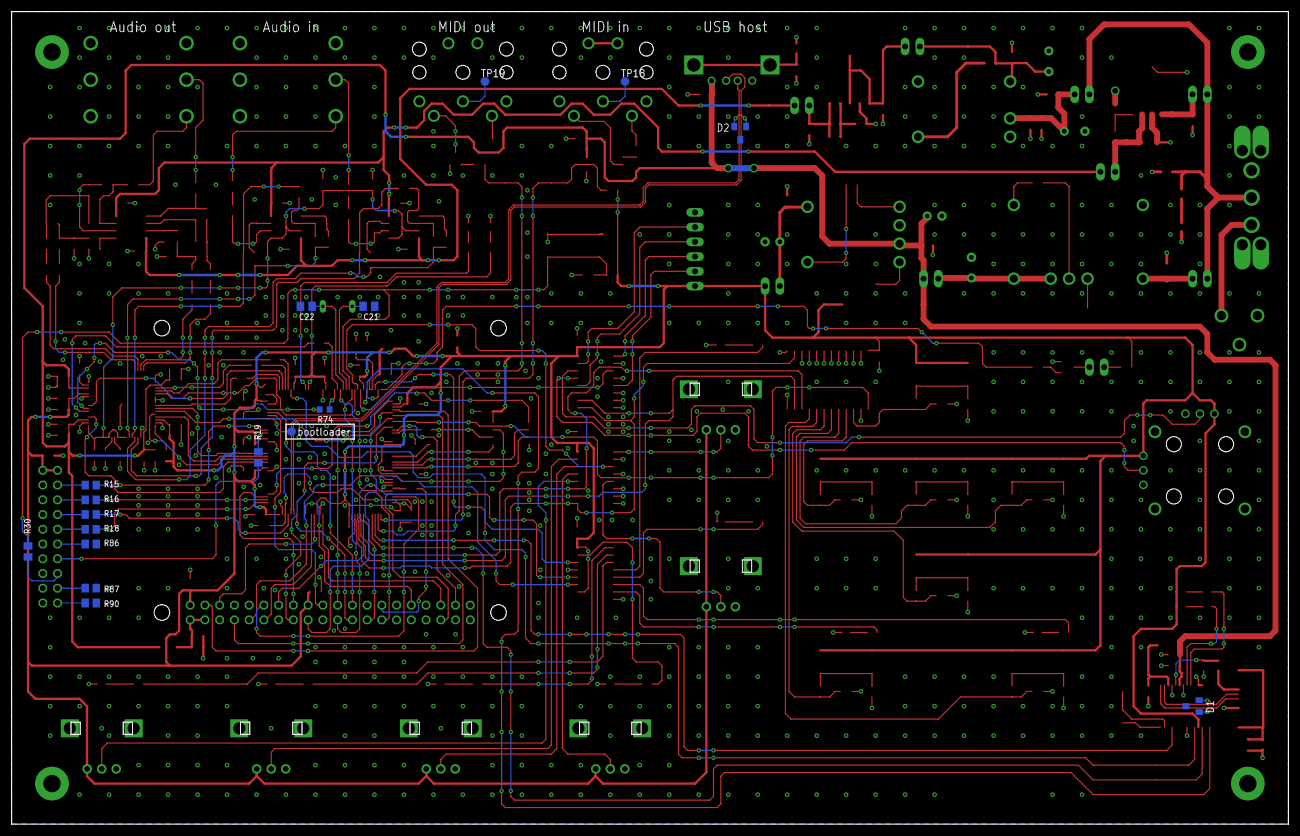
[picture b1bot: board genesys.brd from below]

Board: 2 copper layers, 220.0 x 140.0 mm, 292 parts (17 on the bottom side), 224 nets.

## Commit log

2022-05-27 First upload of the current progress state.
